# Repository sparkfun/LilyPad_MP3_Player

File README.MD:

SparkFun LilyPad MP3
========================================

[*SparkFun LilyPad MP3 (DEV-11013)*](https://www.sparkfun.com/products/11013)

The LilyPad MP3 Player is an amazing little board that contains everything you need to play almost any audio file you wish. You can use it to create MP3-playing hoodies, talking teddy bears, or anything else your imagination can come up with!

### Installation:

You should install the latest version of the Arduino IDE, available at http://www.arduino.cc.

This software requires several nonstandard libraries:
	SdFat (by William Greiman)
	SFEMP3Shield (by Bill Porter)
	pinChangeInt (by Lex Talionis)
	
	The current version of these libraries as of this date are included in this archive.

**TL;DR:** The one-step procedure is to drag the contents of the Arduino folder to your personal Arduino sketch folder. This will create a "libraries" folder (containing support libraries), and a "LilyPad MP3 Player" folder (containing example sketches).

To install the libraries manually, copy the "libraries" folder to your personal Arduino sketch directory. (If there is already a "libraries" folder there, go ahead and add the included libraries to it.) You'll need to restart the Arduino IDE to get it to recognize the new libraries.

To install the example sketches, copy the "LilyPad MP3 Player" folder to your personal Arduino sketch folder.

Loading the sketches:

To load a sketch onto the LilyPad MP3 Player:

1. Connect the LilyPad MP3 Player to your computer using a 5V FTDI board or cable (available at http://www.sparkfun.com). Turn the LilyPad MP3 Player ON. The red LED should light up. Note that a Lipo battery or external power source is required to run the LilyPad MP3 Player.

2. Start the Arduino IDE.

3. Select the correct board type from the menu: Tools / Board / "Arduino Pro or Pro Mini (3.3V, 8MHz) w/ATmega328"

4. Select the correct serial port from the menu: Tools / Serial Port / (the port that your FTDI board or cable has created, usually the highest number)

5. Load the desired sketch into the Arduino IDE.

6. Click on the Upload (right arrow) button at the top of the window. The code should compile then upload to the LilyPad MP3 Player. If you have errors, double-check that you installed the required libraries to the correct place, and restarted the Arduino IDE.

See the tutorials at www.sparkfun.com for more information on using and hacking the LilyPad MP3 Player.

Documentation
--------------
* **[Installing an Arduino Library Guide](https://learn.sparkfun.com/tutorials/installing-an-arduino-library)** - Basic information on how to install an Arduino library.
* **[Hookup Guide](https://learn.sparkfun.com/tutorials/getting-started-with-the-lilypad-mp3-player)** - Basic hookup guide.

License Information
-------------------

This product is _**open source**_! 

Please review the LICENSE.md file for license information. 

If you have any questions or concerns on licensing, please contact support@sparkfun.com.

Distributed as-is; no warranty is given.

- Your friends at SparkFun.

_<COLLABORATION CREDIT>_

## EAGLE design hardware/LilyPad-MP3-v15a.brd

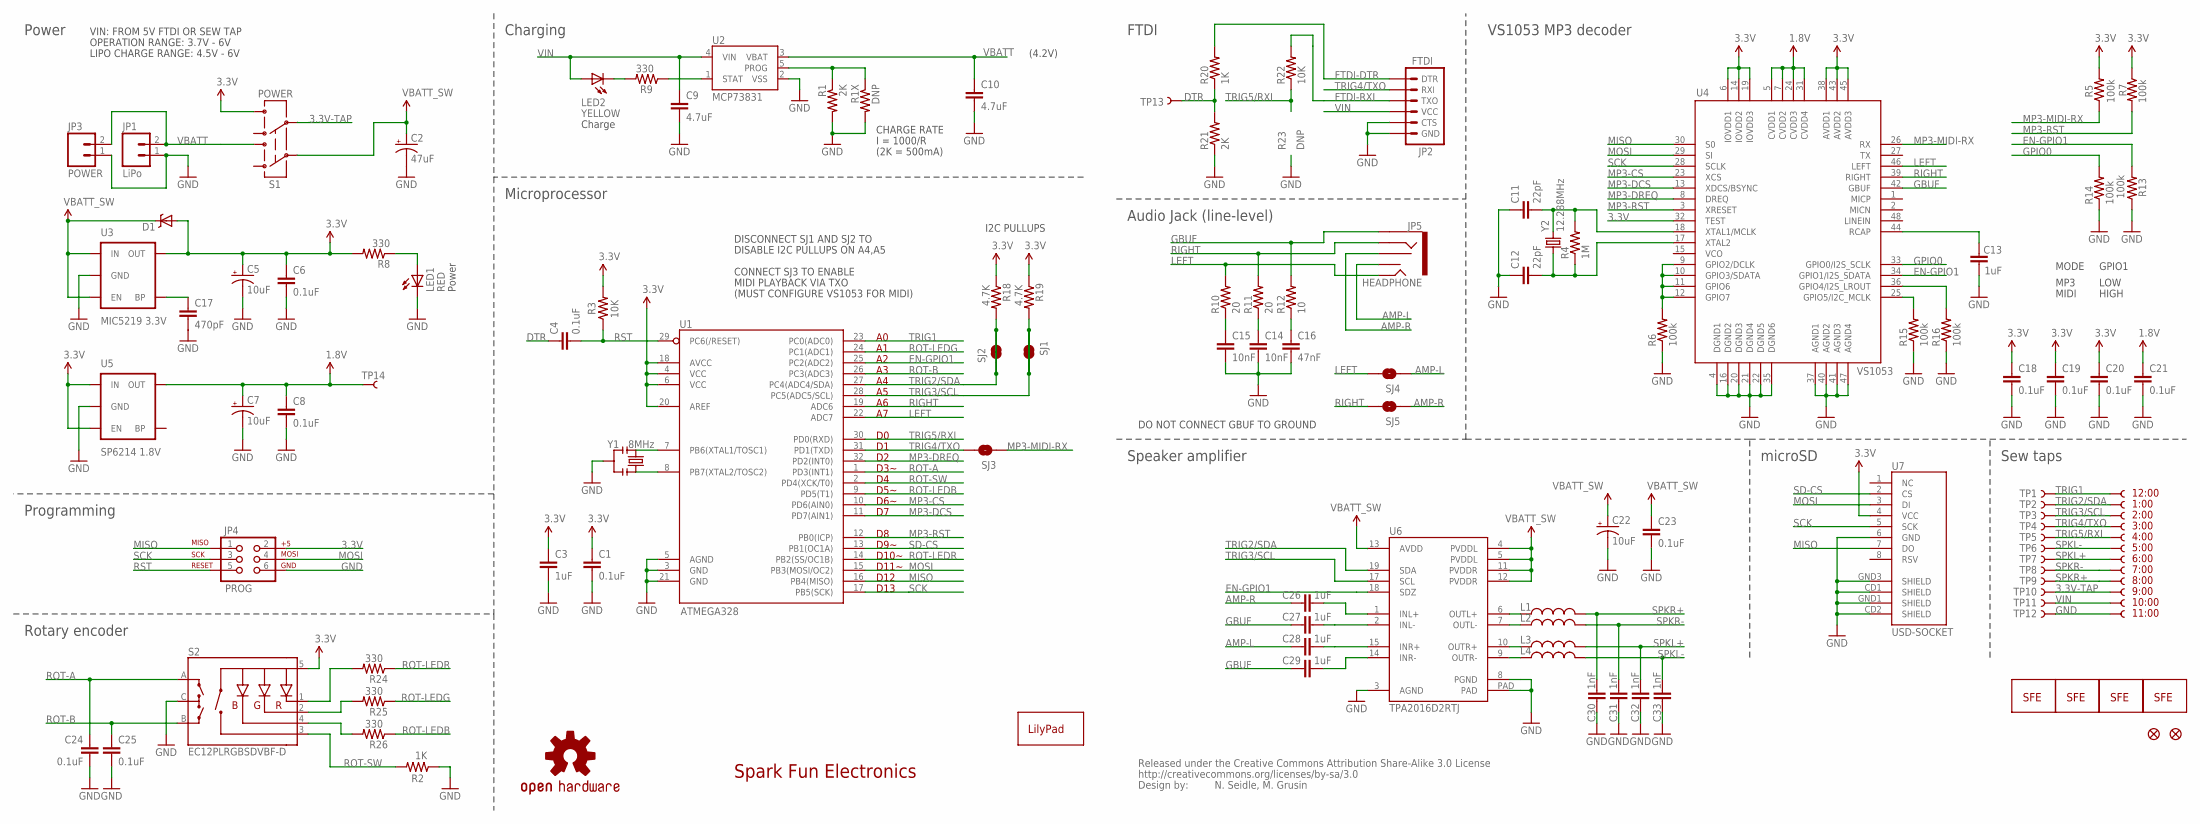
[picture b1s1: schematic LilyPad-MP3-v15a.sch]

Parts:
C1, C4, C6, C8, C18, C19, C20, C21, C23, C24, C25: 0.1uF; 0402-CAP
C2: 47uF; EIA3528
C3, C13, C26, C27, C28, C29: 1uF; 0402-CAP
C5, C7, C22: 10uF; EIA3216
C9, C10: 4.7uF; 0402-CAP
C11, C12: 22pF; 0402-CAP
C14, C15: 10nF; 0402-CAP
C16: 47nF; 0402-CAP
C17: 470pF; 0402-CAP
C30, C31, C32, C33: 1nF; 0402-CAP
D1: DIODE-SCHOTTKY; SOD-523
JP1: LiPo; JST-2-SMD
JP2: FTDI; 1X06-SMD
JP3: POWER; 1X02
JP4: PROG; 2X3-NS
JP5: HEADPHONE; AUDIO-JACK-3.5MM-SMD
JP6: LOGO-SFENW2; SFE-NEW-WEB
JP7, JP8: FIDUCIALUFIDUCIAL; MICRO-FIDUCIAL
L1, L2, L3, L4: INDUCTOR0805; 0805
LED1: RED; LED-0603
LED2: YELLOW; LED-0603
LOGO1, LOGO3: LOGO-SFESK; SFE-LOGO-FLAME
LOGO2: LOGO-SFENEW; SFE-NEW-WEBLOGO
R1, R21: 2K; 0402-RES
R1X: DNP; AXIAL-0.3
R2, R20: 1K; 0402-RES
R3, R22: 10K; 0402-RES
R4: 1M; 0402-RES
R5, R6, R7, R13, R14, R15, R16: 100k; 0402-RES
R8, R9, R24, R25, R26: 330; 0402-RES
R10, R11: 20; 0402-RES
R12: 10; 0402-RES
R18, R19: 4.7K; 0402-RES
S1: POWER; AYZ0202
S2: EC12PLRGBSDVBF-D; ENCODER_LED_3
SJ1, SJ2, SJ3, SJ4, SJ5: SOLDERJUMPERNO; SJ_2S-NO
ST1: TRIG2/SDA; PETAL-LONG-1-2SIDE
ST2: TRIG3/SCL; PETAL-LONG-1-2SIDE
ST3: TRIG4/TXO; PETAL-LONG-1-2SIDE
ST4: TRIG5/RXI; PETAL-LONG-1-2SIDE
ST5: SPKL-; PETAL-LONG-1-2SIDE
ST6: SPKL+; PETAL-LONG-1-2SIDE
ST7: SPKR-; PETAL-LONG-1-2SIDE
ST8: SPKR+; PETAL-LONG-1-2SIDE
ST9: 3.3V; PETAL-LONG-1-2SIDE
ST10: VIN; PETAL-LONG-1-2SIDE
ST11: GND; PETAL-LONG-1-2SIDE
ST12: TRIG1; PETAL-LONG-1-2SIDE
TP1: TRIG1; 1X01NS
TP2: TRIG2/SDA; 1X01NS
TP3: TRIG3/SCL; 1X01NS
TP4: TRIG4/TXO; 1X01NS
TP5: TRIG5/RXI; 1X01NS
TP6: SPKL-; 1X01NS
TP7: SPKL+; 1X01NS
TP8: SPKR-; 1X01NS
TP9: SPKR+; 1X01NS
TP10: 3.3V; 1X01NS
TP11: VIN; 1X01NS
TP12: GND; 1X01NS
TP13: DTR; PAD.03X.05
TP14: 1.8V; PAD.03X.05
U1: ATMEGA328; TQFP32-08
U2: MCP73831; SOT23-5
U3: MIC5219 3.3V; SOT23-5
U4: VS1053; LQFP-48
U5: SP6214 1.8V; SC70
U6: TPA2016D2RTJ; QFN-20-0.5MM
U7: USD-SOCKET; MICRO-SD-SOCKET-PP
U$1: LOGO-LPLP; LOGO-LILYPAD
U$4: OSHW-LOGOM; OSHW-LOGO-M
U$12: CREATIVE_COMMONS
Y1: 8MHz; RESONATOR-SMD
Y2: 12.288MHz; CRYSTAL-SMD-5X3

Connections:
1.8V: C7.A (+), C8.1, C21.1, TP14.P$1, U4.5 (CVDD1), U4.7 (CVDD2), U4.24 (CVDD3), U4.31 (CVDD4), U5.5 (OUT)
3.3V: C1.1, C3.1, C5.A (+), C6.1, C18.1, C19.1, C20.1, D1.A, JP4.2, R3.2, R5.2, R7.1, R8.2, R18.1, R19.1, S1.4 (6), S2.5 (+), U1.4 (VCC), U1.6 (VCC), U1.18 (AVCC), U1.20 (AREF), U3.5 (OUT), U4.6 (IOVDD1), U4.14 (IOVDD2), U4.19 (IOVDD3), U4.32 (TEST), U4.38 (AVDD1), U4.43 (AVDD2), U4.45 (AVDD3), U5.1 (IN), U5.3 (EN), U7.4 (VCC)
3.3V-TAP: S1.5, ST9.1, TP10.1
AMP-L: C28.1, JP5.TSH, SJ4.1
AMP-LX: C26.2, U6.1 (INL+)
AMP-R: C26.1, JP5.RSH, SJ5.1
AMP-RX: C28.2, U6.15 (INR+)
DTR: C4.1, R20.1, R21.2, TP13.P$1
EN-GPIO1: R13.2, U1.25 (PC2(ADC2)), U4.34 (GPIO1/I2S_SDATA), U6.18 (SDZ)
FTDI-DTR: JP2.1 (DTR), R20.2
FTDI-RXI: JP2.3 (TXO), R22.2
G1: R6.2, U4.9 (GPIO2/DCLK), U4.10 (GPIO3/SDATA), U4.11 (GPIO6), U4.12 (GPIO7)
G2: R15.2, U4.25 (GPIO5/I2C_MCLK)
GBUF: C27.1, C29.1, JP5.SLEEVE, R12.2, U4.42 (GBUF)
GBUFLX: C27.2, U6.2 (INL-)
GBUFRX: C29.2, U6.14 (INR-)
GND: C1.2, C2.C (-), C3.2, C5.C (-), C6.2, C7.C (-), C8.2, C9.2, C10.2, C11.1, C12.1, C13.1, C14.2, C15.2, C16.2, C17.2, C18.2, C19.2, C20.2, C21.2, C22.C (-), C23.2, C24.2, C25.2, C30.2, C31.2, C32.2, C33.2, JP1.1, JP2.5 (CTS), JP2.6 (GND), JP3.1, JP4.6, LED1.C, R1.2, R1X.P$2 (2), R2.1, R6.1, R13.1, R14.1, R15.1, R16.1, R21.1, S2.C, ST11.1, TP12.1, U1.3 (GND), U1.5 (AGND), U1.21 (GND), U2.2 (VSS), U3.2 (GND), U4.4 (DGND1), U4.16 (DGND2), U4.20 (DGND3), U4.21 (DGND4), U4.22 (DGND5), U4.35 (DGND6), U4.37 (AGND1), U4.40 (AGND2), U4.41 (AGND3), U4.47 (AGND4), U5.2 (GND), U6.3 (AGND), U6.8 (PGND), U6.PAD, U7.6 (GND), U7.CD1 (SHIELD), U7.CD2 (SHIELD), U7.GND1 (SHIELD), U7.GND3 (SHIELD), Y1.2
GPIO0: R14.2, U4.33 (GPIO0/I2S_SCLK)
LEFT: JP5.TIP, R10.2, SJ4.2, U1.22 (ADC7), U4.46 (LEFT)
MISO: JP4.1, U1.16 (PB4(MISO)), U4.30 (S0), U7.7 (DO)
MOSI: JP4.4, U1.15 (PB3(MOSI/OC2)), U4.29 (SI), U7.3 (DI)
MP3-CS: U1.10 (PD6(AIN0)), U4.23 (XCS)
MP3-DCS: U1.11 (PD7(AIN1)), U4.13 (XDCS/BSYNC)
MP3-DREQ: U1.32 (PD2(INT0)), U4.8 (DREQ)
MP3-MIDI-RX: R5.1, SJ3.1, U4.26 (RX)
MP3-RST: R7.2, U1.12 (PB0(ICP)), U4.3 (XRESET)
unnamed: U1.7 (PB6(XTAL1/TOSC1)), Y1.1
unnamed: U1.8 (PB7(XTAL2/TOSC2)), Y1.3
unnamed: C13.2, U4.44 (RCAP)
unnamed: C16.1, R12.1
unnamed: LED1.A, R8.1
unnamed: C15.1, R10.1
unnamed: LED2.C, R9.2
unnamed: C11.2, R4.2, U4.18 (XTAL1/MCLK), Y2.3 (2)
unnamed: C12.2, R4.1, U4.17 (XTAL2), Y2.1
unnamed: C14.1, R11.1
unnamed: R24.2, S2.1 (-R)
unnamed: R25.2, S2.2 (-G)
unnamed: R26.2, S2.4 (-B)
unnamed: L1.1, U6.6 (OUTL+)
unnamed: L2.1, U6.7 (OUTL-)
unnamed: L3.1, U6.10 (OUTR+)
unnamed: L4.1, U6.9 (OUTR-)
unnamed: C17.1, U3.4 (BP)
unnamed: R16.2, U4.36 (GPIO4/I2S_LROUT)
PROG: R1.1, R1X.P$1 (1), U2.5 (PROG)
RIGHT: JP5.RING, R11.2, SJ5.2, U1.19 (ADC6), U4.39 (RIGHT)
ROT-A: C24.1, S2.A, U1.1 (PD3(INT1))
ROT-B: C25.1, S2.B, U1.26 (PC3(ADC3))
ROT-LEDB: R26.1, U1.9 (PD5(T1))
ROT-LEDG: R25.1, U1.24 (PC1(ADC1))
ROT-LEDR: R24.1, U1.14 (PB2(SS/OC1B))
ROT-SW: R2.2, S2.3 (SW), U1.2 (PD4(XCK/T0))
RST: C4.2, JP4.5, R3.1, U1.29 (PC6(/RESET))
SCK: JP4.3, U1.17 (PB5(SCK)), U4.28 (SCLK), U7.5 (SCK)
SD-CS: U1.13 (PB1(OC1A)), U7.2 (CS)
SPKL+: C32.1, L3.2, ST6.1, TP7.1
SPKL-: C33.1, L4.2, ST5.1, TP6.1
SPKR+: C30.1, L1.2, ST8.1, TP9.1
SPKR-: C31.1, L2.2, ST7.1, TP8.1
STAT: R9.1, U2.1 (STAT)
TRIG1: ST12.1, TP1.1, U1.23 (PC0(ADC0))
TRIG2/SDA: R18.2, SJ2.1, SJ2.2, ST1.1, TP2.1, U1.27 (PC4(ADC4/SDA)), U6.19 (SDA)
TRIG3/SCL: R19.2, SJ1.1, SJ1.2, ST2.1, TP3.1, U1.28 (PC5(ADC5/SCL)), U6.17 (SCL)
TRIG4/TXO: JP2.2 (RXI), SJ3.2, ST3.1, TP4.1, U1.31 (PD1(TXD))
TRIG5/RXI: R22.1, ST4.1, TP5.1, U1.30 (PD0(RXD))
VBATT: C10.1, JP1.2, JP3.2, S1.1 (3), U2.3 (VBAT)
VBATT_SW: C2.A (+), C22.A (+), C23.1, D1.C, S1.2, U3.1 (IN), U3.3 (EN), U6.4 (PVDDL), U6.5 (PVDDL), U6.11 (PVDDR), U6.12 (PVDDR), U6.13 (AVDD)
VIN: C9.1, JP2.4 (VCC), LED2.A, ST10.1, TP11.1, U2.4 (VIN)

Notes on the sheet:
Spark Fun Electronics
N. Seidle, M. Grusin
microSD
Power
Audio Jack (line-level)
VS1053 MP3 decoder
Charging
FTDI
Sew taps
Speaker amplifier
D3~
D5~
D6~
D9~
D10~
D11~
D12
D13
1:00
12:00
Programming
Rotary encoder
GPIO1
LOW
HIGH
MODE
MP3
MIDI
Microprocessor
2:00
3:00
4:00
5:00
6:00
7:00
8:00
9:00
10:00
11:00
OPERATION RANGE: 3.7V - 6V

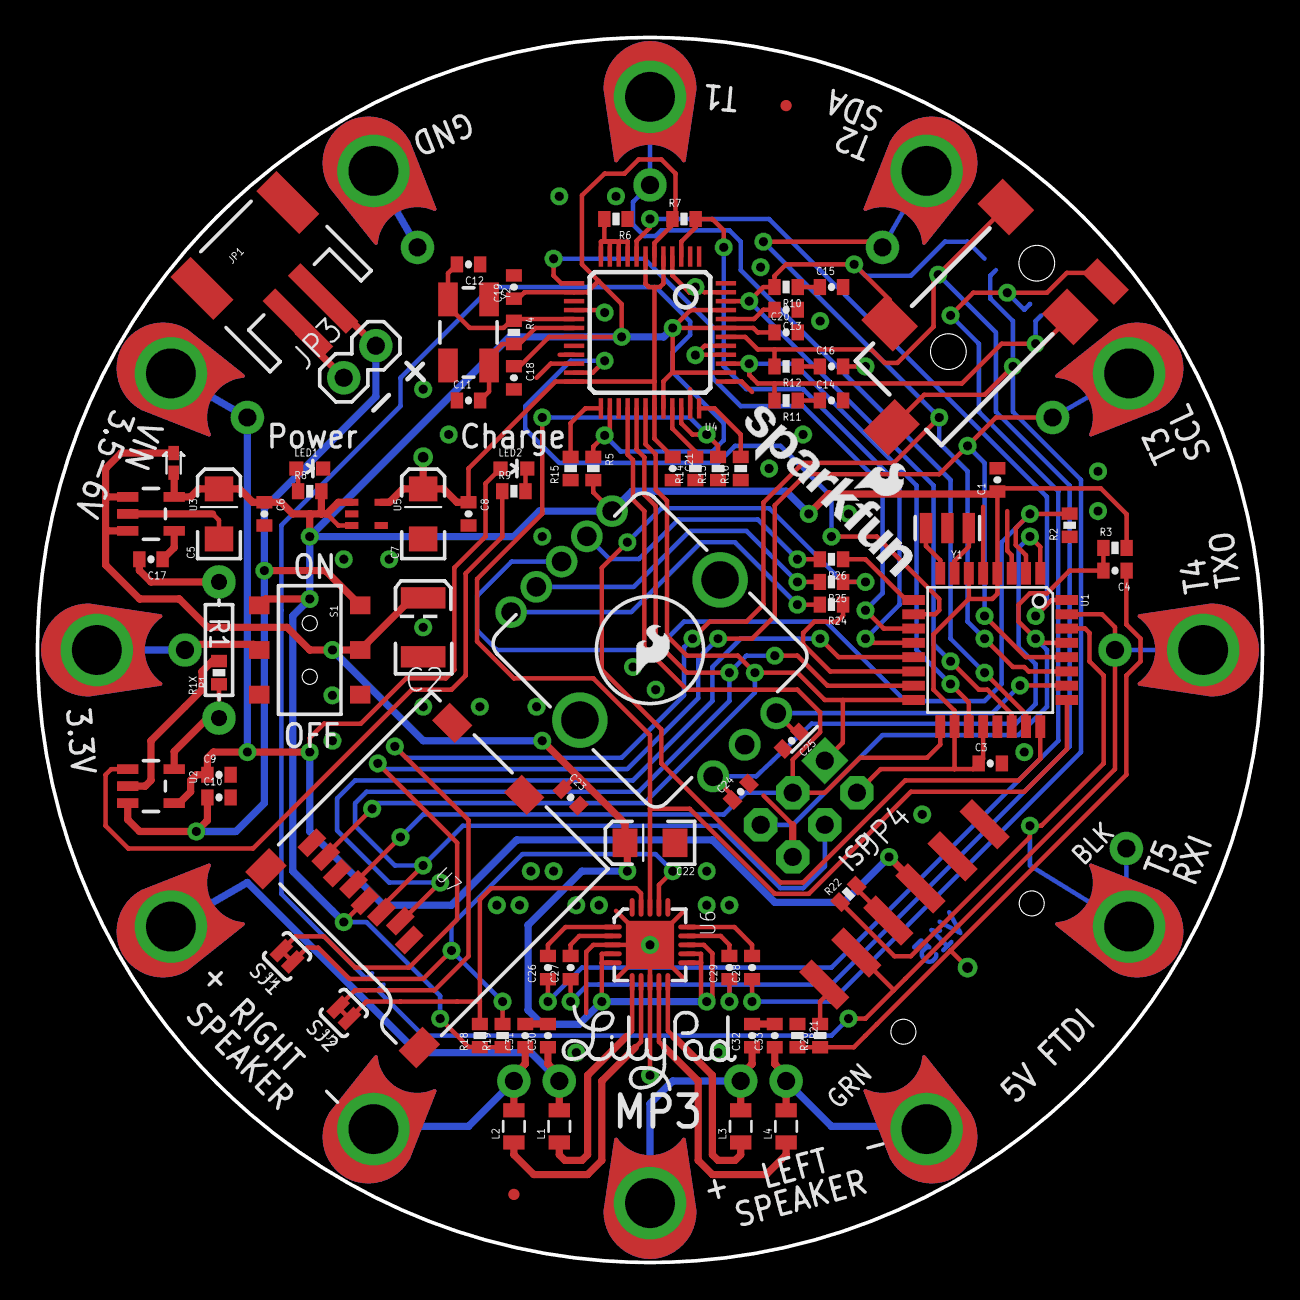
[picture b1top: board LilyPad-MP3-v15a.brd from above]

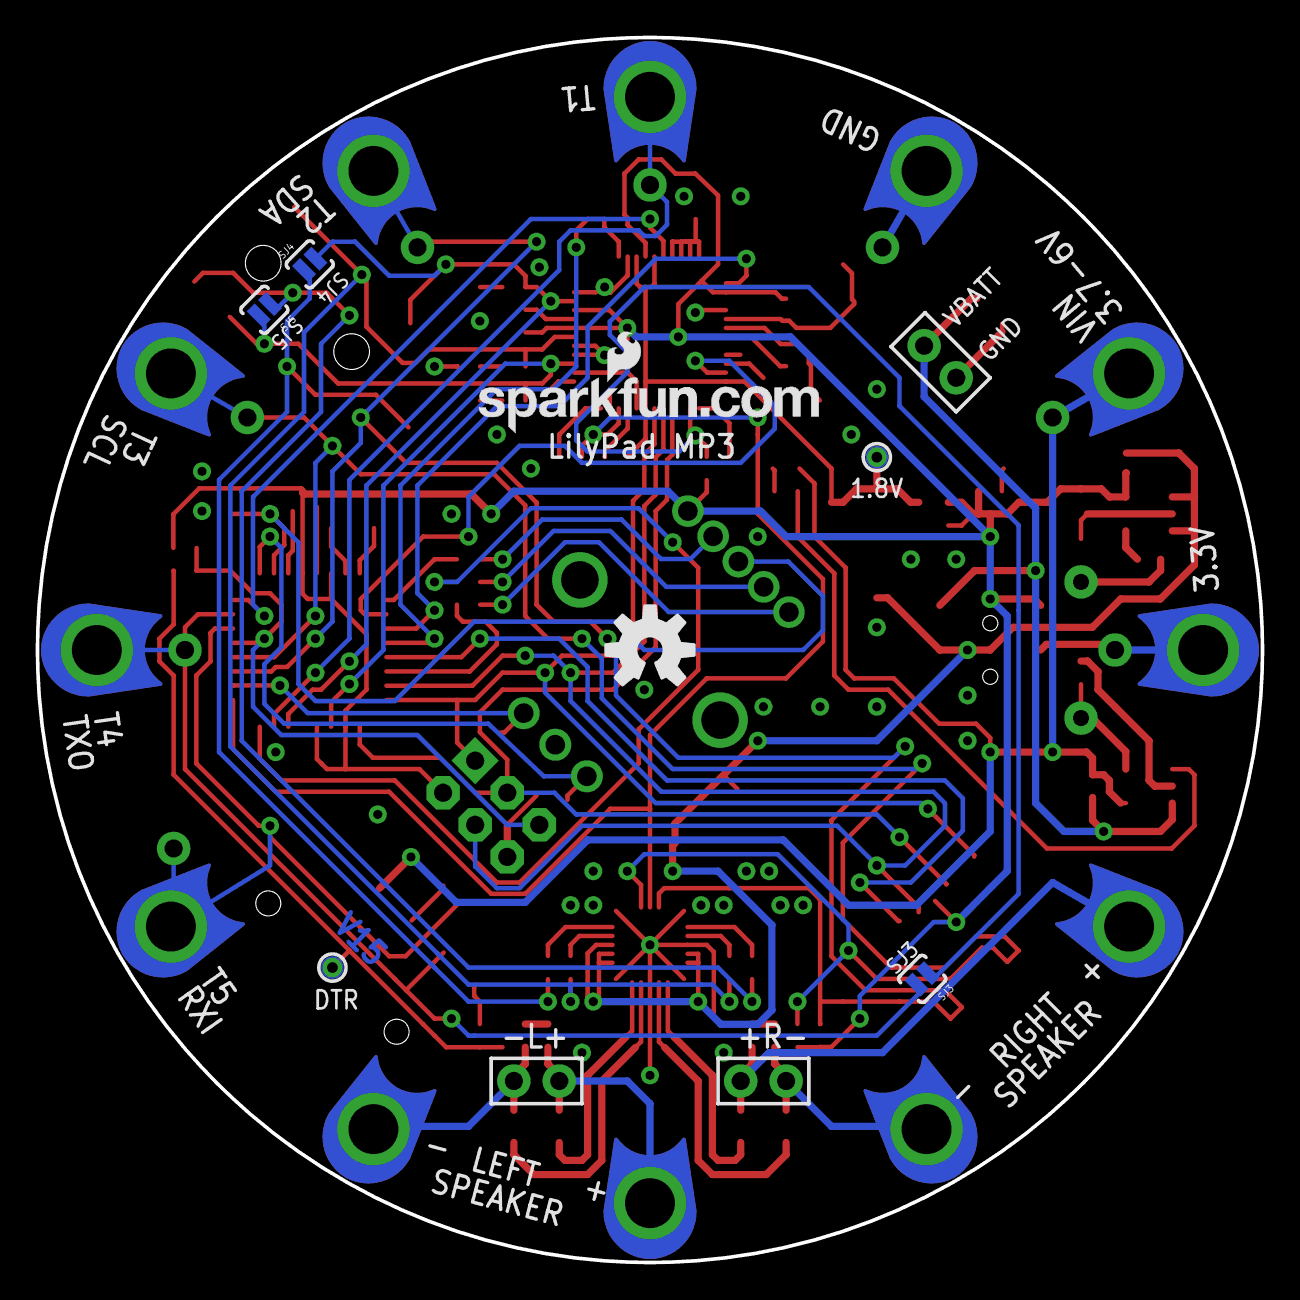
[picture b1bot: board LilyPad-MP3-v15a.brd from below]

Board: 2 copper layers, 68.6 x 68.6 mm, 121 parts (7 on the bottom side), 69 nets.

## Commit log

2013-05-02 modified schematic for two pages, created PDF
2013-05-02 Improved comments on rotary_encoder_demo
2013-05-10 Updated SdFat library to 20130313 for Arduino 1.0.4
    This update fixes an issue where compiling software using the SdFat
    library under Arduino 1.0.4 failed. The updated SdFat library includes a
    new version of FreeRam() that has been modified to use Arduino's new
    implementation of malloc(). See
    http://arduino.cc/forum/index.php?topic=154033.0 for more information.
2015-10-13 Updating repo structure, moving library files
2015-10-13 Squashed 'Libraries/Arduino/PinChangeInit/' content from commit cd9ff71
    git-subtree-dir: Libraries/Arduino/PinChangeInit
    git-subtree-split: cd9ff714a291451a6dfabf0aee3eee09b828757c
2015-10-13 Squashed 'Libraries/Arduino/SdFat/' content from commit fe80cc3
    git-subtree-dir: Libraries/Arduino/SdFat
    git-subtree-split: fe80cc35c4186f22bdd4f15059caebbeac0d7ce9
2015-10-13 Squashed 'Libraries/Arduino/TPA2016D2/' content from commit 623864a
    git-subtree-dir: Libraries/Arduino/TPA2016D2
    git-subtree-split: 623864adb40d791550927f8a84d3bab9669ac588
2015-10-13 Squashed 'Libraries/Arduino/MP3Player/' content from commit ed7d8fb
    git-subtree-dir: Libraries/Arduino/MP3Player
    git-subtree-split: ed7d8fb3a5008f14d7e872d9e77ae0dbf00b5098
2015-10-13 Updating MP3 library to current version
2015-10-13 Updating examples folder structure
2015-12-09 Fixes compilation on newer versions of Arduino.
2016-02-29 Updated sfe mp3 player to most recent version
    This fixes compiler errors on recent Arduino IDE (1.6.7 etc.)
2018-12-19 Rename README.txt to README.MD
2025-06-27 Update SFEMP3Shieldmainpage.h
    Updating links

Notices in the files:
parts and their libraries:
SparkFun: Released under the Creative Commons Attribution Share-Alike 3.0 License
SparkFun: http://creativecommons.org/licenses/by-sa/3.0
SparkFun-Passives: Licensing: CC v3.0 Share-Alike You are welcome to use this library for commercial purposes.
